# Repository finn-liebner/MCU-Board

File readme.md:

## MCU-Board

### Bauteile

| Stückzahl | Mouser                                                                       |
|-----------|------------------------------------------------------------------------------|
| 1x        | [ESP WROOM 32D](https://www.mouser.de/ProductDetail/356-ESPWROOM3200PS3)     |
| 2x        | [Taster](https://www.mouser.de/ProductDetail/506-FSM4JH)                     |
| 1x        | [Schalter](https://www.mouser.de/ProductDetail/611-JS202011CQN)              |
| 1x        | [LDO 3.3V](https://www.mouser.de/ProductDetail/621-AZ1117IH-3.3TRG1)         |
| 1x        | [Step-Down 5.0V](https://www.mouser.de/ProductDetail/621-AP1509-50SG-13)     |
| 1x        | [Spule 47µH](https://www.mouser.de/ProductDetail/815-AIUR-08-470K)           |
| 3x        | [Schottkydiode](https://www.mouser.de/ProductDetail/750-SS34B-HF)            |
| 1x        | [Zenerdiode 3.3V](https://www.mouser.de/ProductDetail/621-MMSZ5226B-F)       |
| 3x        | [LED Rot](https://www.mouser.de/ProductDetail/720-LHR974-LP-1)               |
| 1x        | [LED Grün](https://www.mouser.de/ProductDetail/720-LGR971-KN-1)              |
| 8x        | [Kondensator 100nF](https://www.mouser.de/ProductDetail/963-UMK212BJ104MG-T) |
| 6x        | [Kondensator 10µF](https://www.mouser.de/ProductDetail/963-UMK325C7106KM-T)  |
| 4x        | [Widerstand 82Ω](https://www.mouser.de/ProductDetail/71-CRCW0805-82-E3)      |
| 2x        | [Widerstand 4.7kΩ](https://www.mouser.de/ProductDetail/71-CRCW0805-4.7K-E3)  |
| 1x        | [Widerstand 36kΩ](https://www.mouser.de/ProductDetail/71-CRCW080536K0FKEA)   |
| 1x        | [Anschlussblock](https://www.mouser.de/ProductDetail/649-220316-H041B01LF)   |
| 1x        | Steckleiste / 2.54 / 4-Pin                                                   |

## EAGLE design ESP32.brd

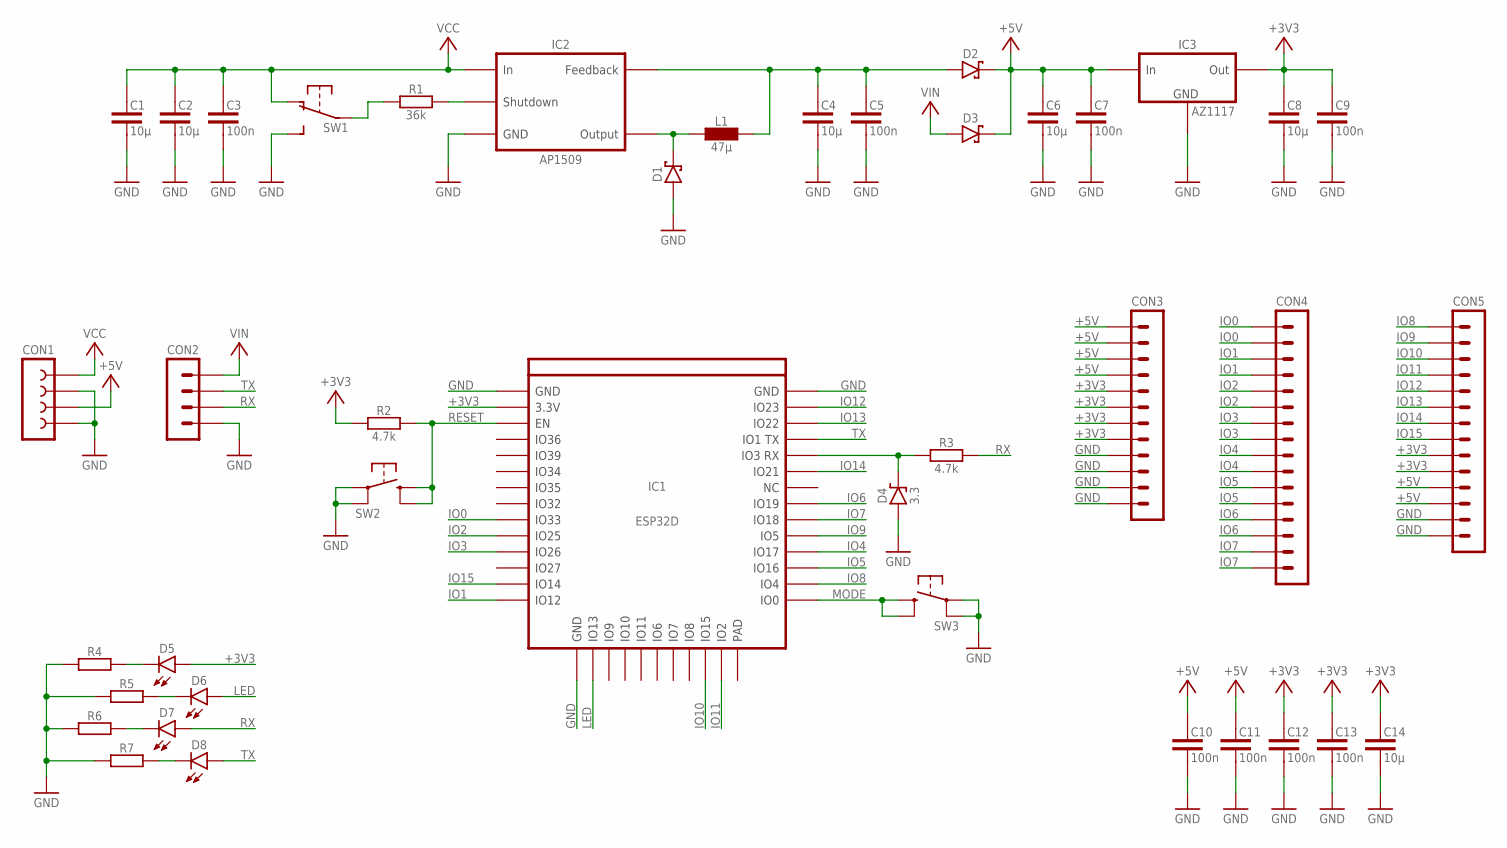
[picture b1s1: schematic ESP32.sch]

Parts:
C1, C2, C4, C6, C8, C14: 10µ; C1210
C3, C5, C7, C9, C10, C11, C12, C13: 100n; C0805
CON1: CON-4
CON2: PIN-4
D1, D2, D3: D-SCHOTTKY; DO214AA-2
D4: 3.3; SOD123-2
D5, D6, D7, D8: LED; D0805
IC1: ESP32D; ESP32
IC2: AP1509; SO8
IC3: AZ1117; SOT223
L1: 47µ; L6
P1, P2, P15, P16: 5V; PAD
P3, P4, P17, P18: 3V; PAD
P5, P6, P19, P20: 0V; PAD
P7, P21: IO0; PAD
P8, P22: IO1; PAD
P9, P23: IO2; PAD
P10, P24: IO3; PAD
P11, P25: IO4; PAD
P12, P26: IO5; PAD
P13, P27: IO6; PAD
P14, P28: IO7; PAD
P30: IO8; PAD2
P31: IO9; PAD2
P32: IO10; PAD2
P33: IO11; PAD2
P34: IO12; PAD2
P35: IO13; PAD2
P39, P45: 5V; PAD2
P40, P44: 3V; PAD2
P41, P46: 0V; PAD2
P42: IO14; PAD2
P43: IO15; PAD2
R1: 36k; R0805
R2, R3: 4.7k; R0805
R4, R5, R6, R7: R; R0805
SW1: SW1
SW2, SW3: SW2

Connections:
+3V3: C8.1, C9.1, C12.1, C13.1, C14.1, D5.A, IC1.2 (3.3V), IC3.2 (OUT), IC3.4 (OUT), P3.1, P4.1, P17.1, P18.1, P40.P$1, P44.P$1, R2.1
+5V: C6.1, C7.1, C10.1, C11.1, CON1.3, D2.K (C), D3.K (C), IC3.3 (VCC), P1.1, P2.1, P15.1, P16.1, P39.P$1, P45.P$1
GND: C1.2, C2.2, C3.2, C4.2, C5.2, C6.2, C7.2, C8.2, C9.2, C10.2, C11.2, C12.2, C13.2, C14.2, CON1.2, CON1.4, CON2.4, D1.A, D4.A, IC1.1 (GND0), IC1.15 (GND1), IC1.38 (GND2), IC2.5 (GND), IC2.6 (GND), IC2.7 (GND), IC2.8 (GND), IC3.1 (GND), P5.1, P6.1, P19.1, P20.1, P41.P$1, P46.P$1, R4.2, R5.2, R6.2, R7.2, SW1.3 (2), SW1.6 (2), SW2.1 (P0), SW2.3 (P1), SW3.1 (P0), SW3.3 (P1)
IO0: IC1.9 (IO33), P7.1, P21.1
IO1: IC1.14 (IO12), P8.1, P22.1
IO2: IC1.10 (IO25), P9.1, P23.1
IO3: IC1.11 (IO26), P10.1, P24.1
IO4: IC1.28 (IO17), P11.1, P25.1
IO5: IC1.27 (IO16), P12.1, P26.1
IO6: IC1.31 (IO19), P13.1, P27.1
IO7: IC1.30 (IO18), P14.1, P28.1
IO8: IC1.26 (IO4), P30.P$1
IO9: IC1.29 (IO5), P31.P$1
IO10: IC1.23 (IO15), P32.P$1
IO11: IC1.24 (IO2), P33.P$1
IO12: IC1.37 (IO23), P34.P$1
IO13: IC1.36 (IO22), P35.P$1
IO14: IC1.33 (IO21), P42.P$1
IO15: IC1.13 (IO14), P43.P$1
LED: D6.A, IC1.16 (IO13)
MODE: IC1.25 (IO0), SW3.2 (S0), SW3.4 (S1)
unnamed: IC2.4 (SHDN), R1.2
unnamed: D1.K (C), IC2.2 (OUT), L1.1
unnamed: R1.1, SW1.2 (C), SW1.5 (C)
unnamed: C4.1, C5.1, D2.A, IC2.3 (FB), L1.2
unnamed: D5.K, R4.1
unnamed: D4.K (C), IC1.34 (IO3), R3.1
unnamed: D6.K, R5.1
unnamed: D7.K, R6.1
unnamed: D8.K, R7.1
RESET: IC1.3 (EN), R2.2, SW2.2 (S0), SW2.4 (S1)
RX: CON2.3, D7.A, R3.2
TX: CON2.2, D8.A, IC1.35 (IO1)
VCC: C1.1, C2.1, C3.1, CON1.1, IC2.1 (IN), SW1.1, SW1.4 (1)
VIN: CON2.1, D3.A

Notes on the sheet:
CON3
CON4
CON5

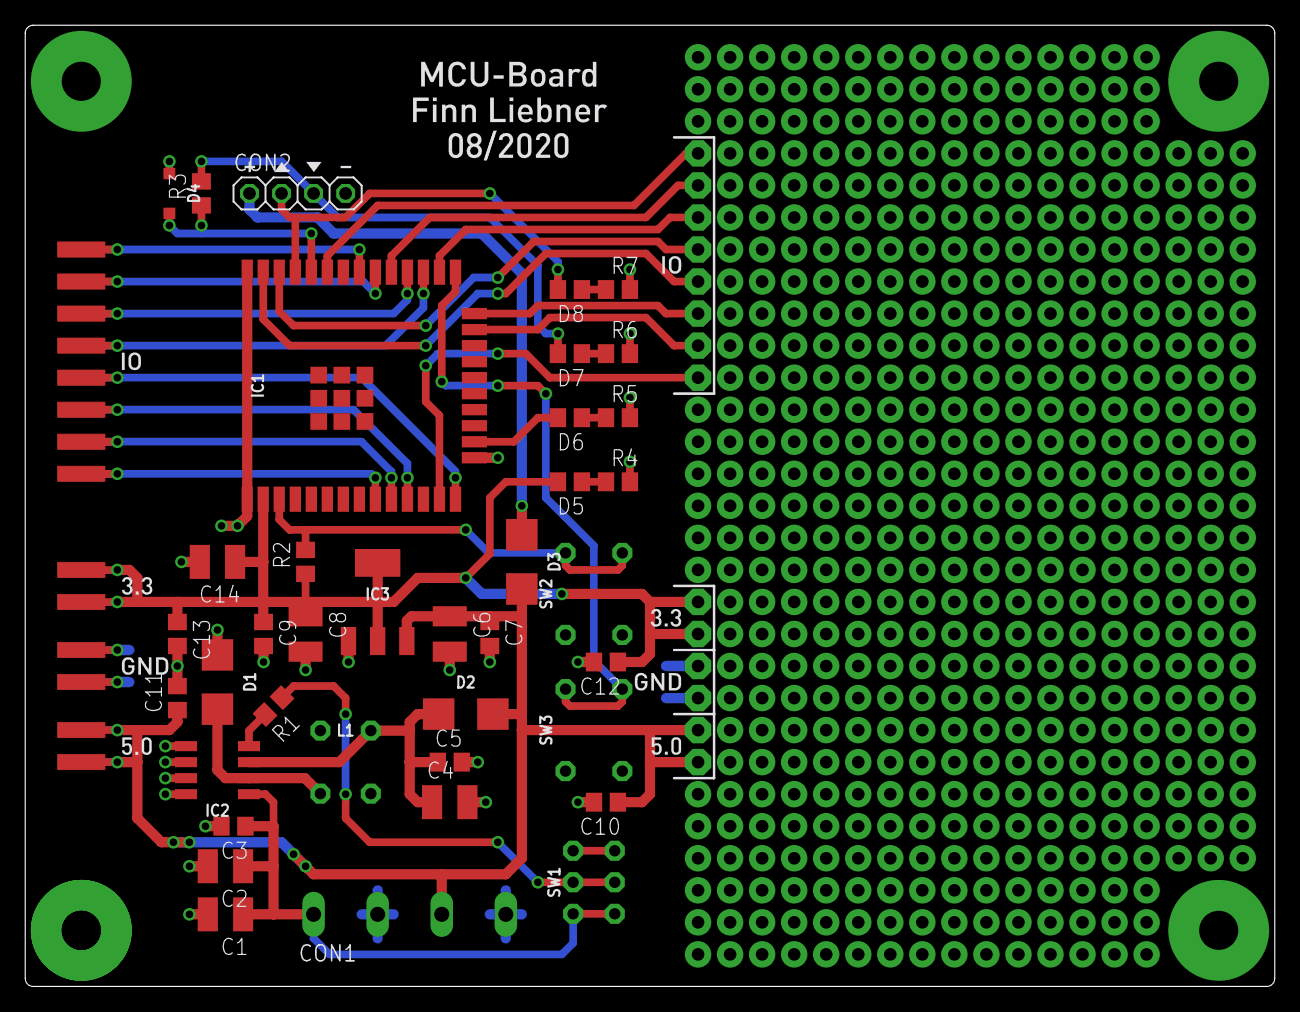
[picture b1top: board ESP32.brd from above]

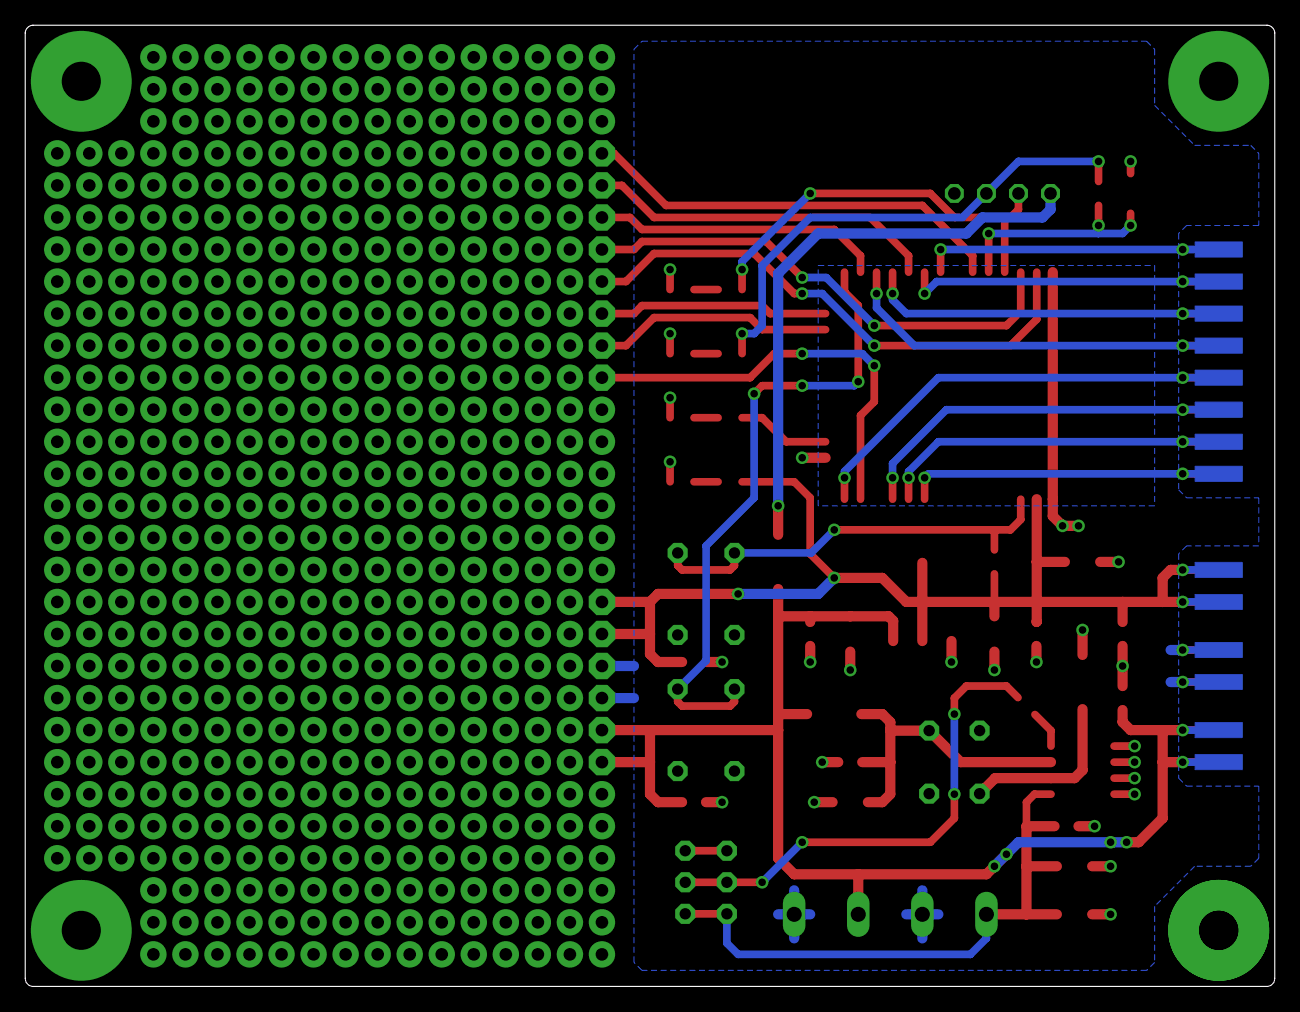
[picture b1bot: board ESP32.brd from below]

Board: 2 copper layers, 99.1 x 76.2 mm, 80 parts (14 on the bottom side), 35 nets.

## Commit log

2020-08-18 Update to v2
2020-08-18 Removed files from v1
